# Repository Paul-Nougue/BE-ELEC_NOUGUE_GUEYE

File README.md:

# BE-ELEC_NOUGUE_GUEYE
3IMACS D

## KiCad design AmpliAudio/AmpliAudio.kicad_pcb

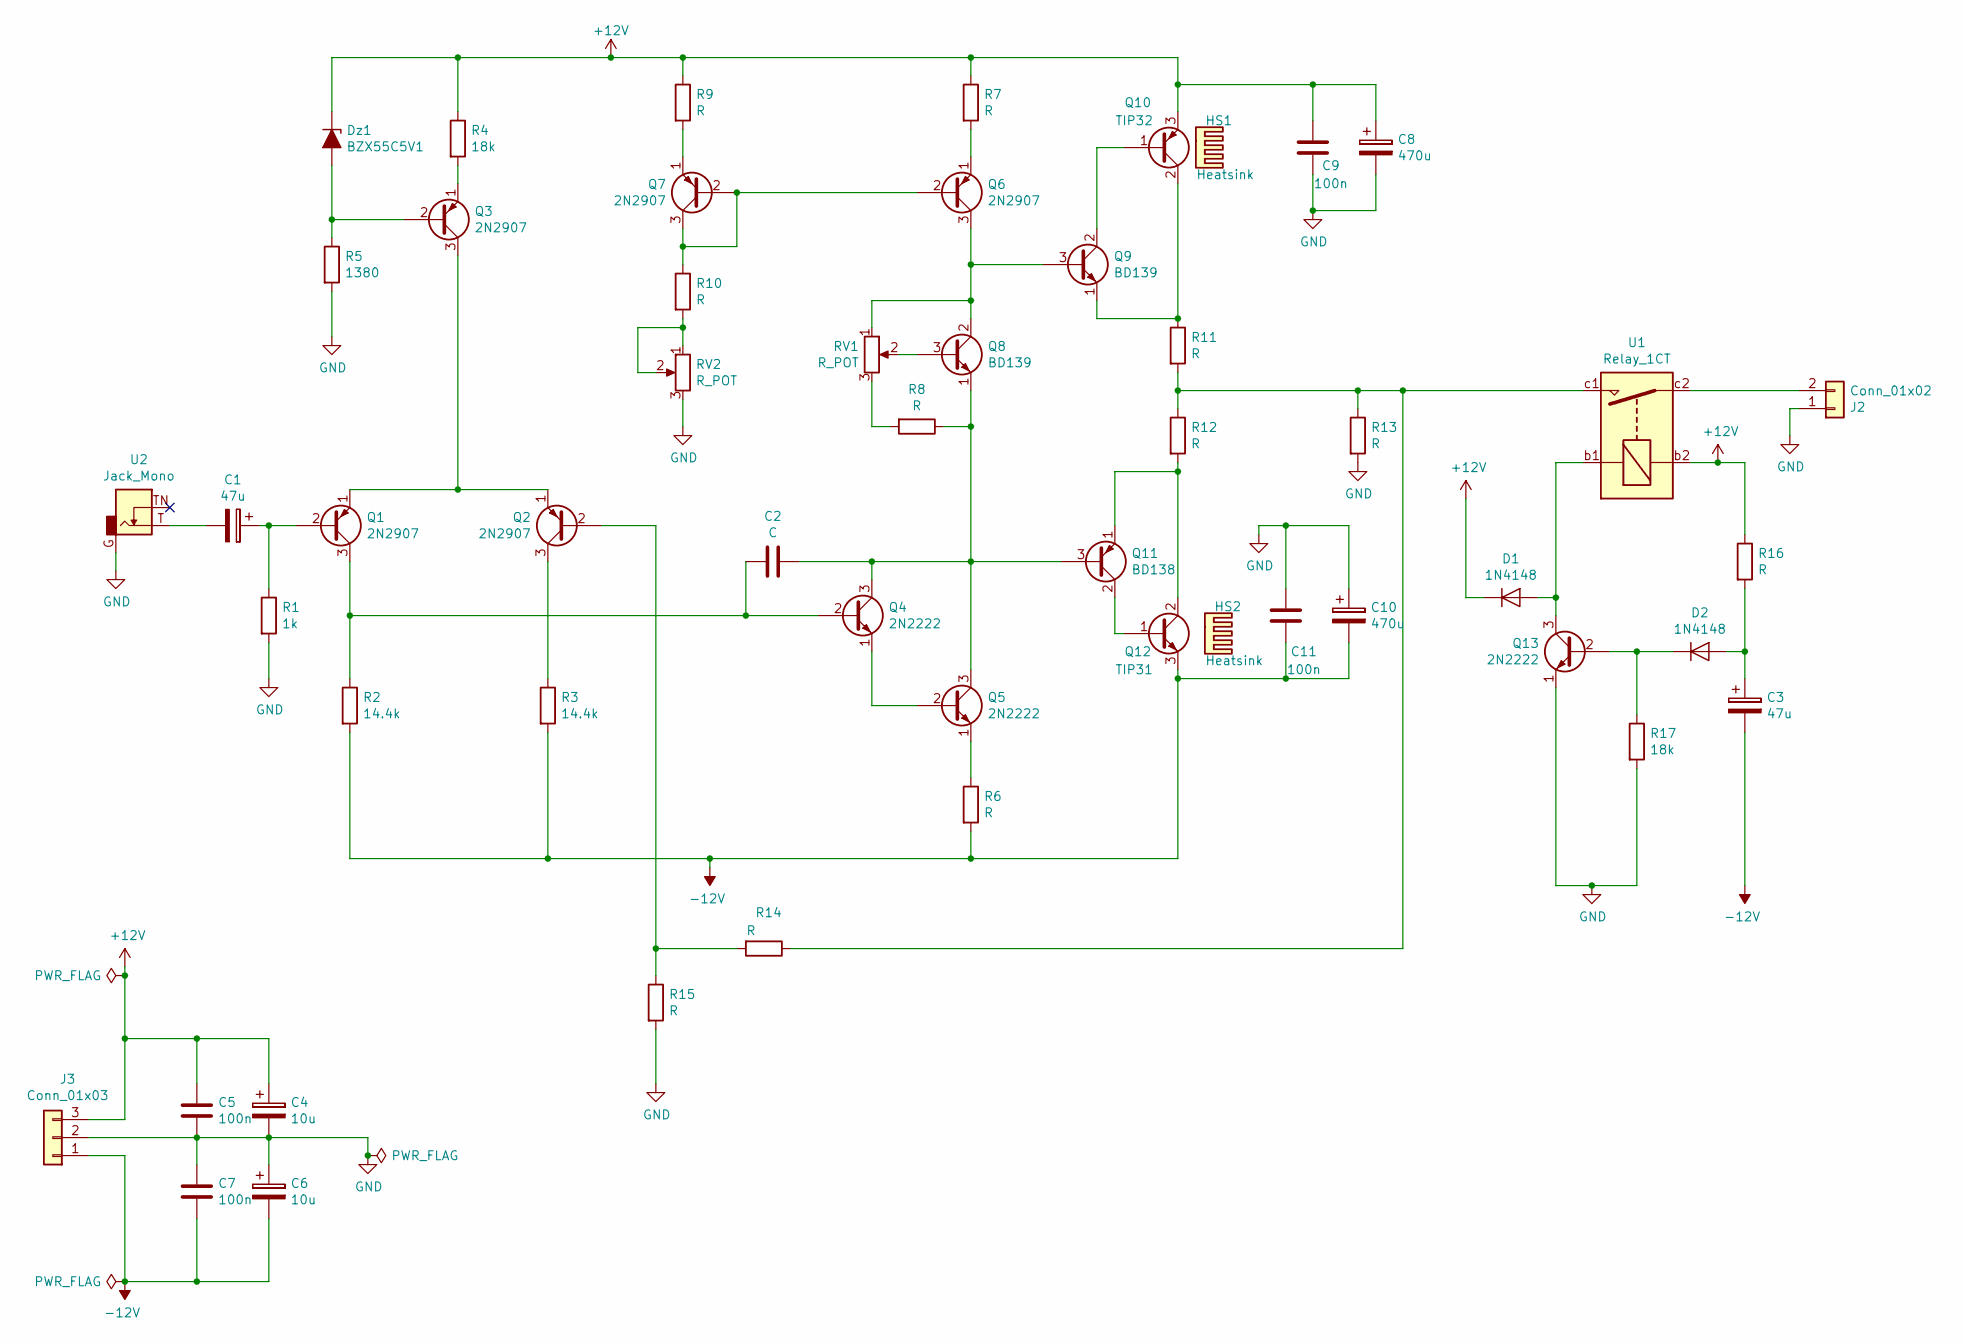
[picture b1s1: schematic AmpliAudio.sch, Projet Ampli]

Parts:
C1, C3: 47u; CP_Radial_D8.0mm_P5.00mm
C2: C; C_Rect_L7.2mm_W3.5mm_P5.00mm_FKS2_FKP2_MKS2_MKP2
C4, C6: 10u; CP_Radial_D8.0mm_P5.00mm
C5, C7, C9, C11: 100n; C_Rect_L7.2mm_W3.5mm_P5.00mm_FKS2_FKP2_MKS2_MKP2
C8, C10: 470u; CP_Radial_D12.5mm_P5.00mm
D1, D2: 1N4148; D_DO-35_SOD27_P10.16mm_Horizontal
Dz1: BZX55C5V1; D_DO-35_SOD27_P10.16mm_Horizontal
HS1, HS2: Heatsink; Heatsink_Fischer_SK104-STC-STIC_35x13mm_2xDrill2.5mm
J2: Conn_01x02; PhoenixContact_MSTBVA_2,5_2-G-5,08_1x02_P5.08mm_Vertical
J3: Conn_01x03; PhoenixContact_MSTBVA_2,5_3-G-5,08_1x03_P5.08mm_Vertical
Q1, Q2, Q3, Q6, Q7: 2N2907; TO-18-3
Q4, Q5, Q13: 2N2222; TO-18-3
Q8, Q9: BD139; TO-126-3_Vertical
Q10: TIP32; TO-220-3_Vertical
Q11: BD138; TO-126-3_Vertical
Q12: TIP31; TO-220-3_Vertical
R1: 1k; R_Axial_DIN0207_L6.3mm_D2.5mm_P10.16mm_Horizontal
R2, R3: 14.4k; R_Axial_DIN0207_L6.3mm_D2.5mm_P10.16mm_Horizontal
R4, R17: 18k; R_Axial_DIN0207_L6.3mm_D2.5mm_P10.16mm_Horizontal
R5: 1380; R_Axial_DIN0207_L6.3mm_D2.5mm_P10.16mm_Horizontal
R6, R7, R8, R9, R10, R13, R14, R15, R16: R; R_Axial_DIN0207_L6.3mm_D2.5mm_P10.16mm_Horizontal
R11, R12: R; R_Axial_DIN0516_L15.5mm_D5.0mm_P20.32mm_Horizontal
RV1, RV2: R_POT; Potentiometer_Bourns_3296W_Vertical
U1: Relay_1CT; Relais_112LMH2
U2: Jack_Mono; Jack_35RAPC2AV

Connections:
+12V: C4.1, C5.1, C8.1, C9.2, D1.1 (K), Dz1.1 (K), J3.3, Q10.3 (E), R4.1, R7.1, R9.1, R16.1, U1.b2
-12V: C3.2, C6.2, C7.2, C10.2, C11.1, J3.1, Q12.3 (E), R2.2, R3.2, R6.2
GND: C4.2, C5.2, C6.1, C7.1, C8.2, C9.1, C10.1, C11.2, J2.1, J3.2, Q13.1 (E), R1.2, R5.2, R13.2, R15.2, R17.2, RV2.3, U2.G
unnamed: C1.1, Q1.2 (B), R1.1
unnamed: C1.2, U2.T
unnamed: C2.1, Q4.3 (C), Q5.3 (C), Q8.1 (E), Q11.3 (B), R8.1
unnamed: C2.2, Q1.3 (C), Q4.2 (B), R2.1
unnamed: C3.1, D2.2 (A), R16.2
unnamed: D1.2 (A), Q13.3 (C), U1.b1
unnamed: D2.1 (K), Q13.2 (B), R17.1
unnamed: Dz1.2 (A), Q3.2 (B), R5.1
unnamed: J2.2, U1.c2
unnamed: Q1.1 (E), Q2.1 (E), Q3.3 (C)
unnamed: Q2.2 (B), R14.2, R15.1
unnamed: Q2.3 (C), R3.1
unnamed: Q3.1 (E), R4.2
unnamed: Q4.1 (E), Q5.2 (B)
unnamed: Q5.1 (E), R6.1
unnamed: Q6.1 (E), R7.2
unnamed: Q6.2 (B), Q7.2 (B), Q7.3 (C), R10.1
unnamed: Q6.3 (C), Q8.2 (C), Q9.3 (B), RV1.1
unnamed: Q7.1 (E), R9.2
unnamed: Q8.3 (B), RV1.2
unnamed: Q9.2 (C), Q10.1 (B)
unnamed: Q9.1 (E), Q10.2 (C), R11.1
unnamed: Q11.1 (E), Q12.2 (C), R12.2
unnamed: Q11.2 (C), Q12.1 (B)
unnamed: R8.2, RV1.3
unnamed: R10.2, RV2.1, RV2.2
unnamed: R11.2, R12.1, R13.1, R14.1, U1.c1

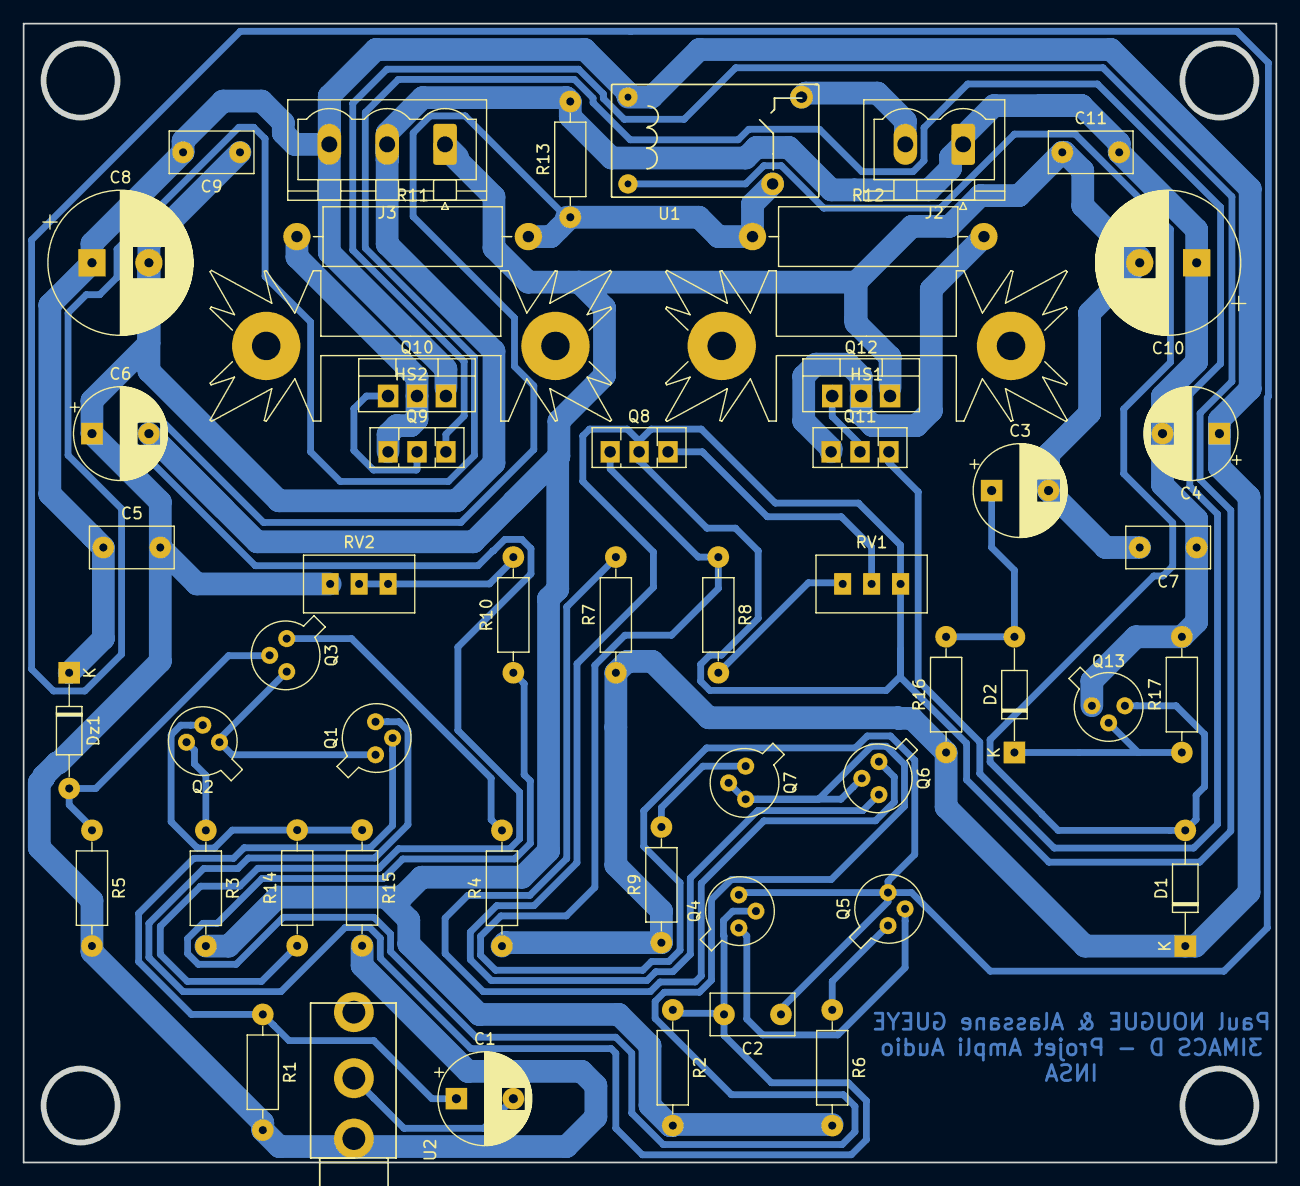
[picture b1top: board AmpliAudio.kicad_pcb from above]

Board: 2 copper layers, 110.0 x 100.0 mm, 52 parts (0 on the bottom side), 30 nets.

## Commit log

2020-04-02 ajout github
2020-04-09 avis placement
2020-04-16 Avis routage
2020-04-17 Version Finale
